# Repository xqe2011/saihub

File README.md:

<h1 align="center">
   SAIHub
</h1>

<p align="center"><strong>Give your agent a hand.</strong></p>

<p align="center">
  An MIT-licensed, agent-ready IO board.<br>
  ESP32-C5 firmware that speaks <a href="https://modelcontextprotocol.io/">MCP</a>,
  so Cursor, Claude Code, and Codex can drive real hardware.
</p>

<p align="center">
  <a href="README.zh.md">中文</a>
  · <a href="docs/cookbook.md">Cookbook</a>
  · <a href="docs/hardware.md">Hardware</a>
  · <a href="docs/design-notes.md">Protocol</a>
  · <a href="docs/build.md">Build</a>
  · <a href="https://github.com/xqe2011/saihub/releases">Releases</a>
  · <a href="LICENSE">MIT</a>
</p>

<p align="center">
  Watch the video: <a href="https://youtu.be/VpJexyDZVVk"> YouTube</a>
  · <a href="https://www.bilibili.com/video/BV1MVn66EEgq"> Bilibili</a>
</p>

---

## What it is

SAIHub is a pocket IO and debug companion for coding agents. Flash it, join Wi-Fi, paste an MCP URL, and the agent gets a hand on real hardware:

- **Wireless flashing & debugging** — expose CMSIS-DAP (SWD) and RFC2217 (serial-over-TCP) on the LAN or through the cloud relay, so OpenOCD, GDB, and serial flashers can program and step-debug targets like STM32, RP2040, nRF52, Arduino, or ESP32 remotely.
- **Bus debugging & emulation** — probe and drive UART, SPI, and I2C buses directly, or run SPI and I2C in slave mode to capture bus transactions from the target and emulate sensors or peripherals with programmable response maps.
- **GPIO / PWM / trace / programmable power** — toggle pins, generate pulses and PWM up to 50 kHz, capture multi-pin edges like a logic analyzer, and switch fault-protected 3.3 V / 5 V rails on and off, all over MCP.
- **On-device scripting** — the agent can upload Lua scripts and run them on the board itself, so timing-critical or multi-step logic executes locally without a network round-trip per operation.

The board is **SAIHub-Mini**: 48 × 28 mm, ESP32-C5, USB-C, a 12-pin header, fault-latched programmable 3.3 V / 5 V outputs, and an onboard buzzer. Pinout and electrical details: [docs/hardware.md](docs/hardware.md). Firmware, KiCad design, and the relay server all live in this repo.

You do not have to use our board — the firmware runs on any ESP32-C5. See [bring your own board](docs/bring-your-own-board.md) for what changes and where to remap the GPIOs.

## What you can do with it

**Zero-PC firmware development with cloud agents.** You don't even need a computer at the bench. Power SAIHub from a USB charger, wire it to your target board, and connect **Cursor Cloud Agents**, **Claude Code cloud sessions**, or **OpenAI Codex Cloud** through the cloud relay. Running entirely in the cloud, the agent can:

1. **Provision the build & debug environment** in its cloud sandbox — install toolchains, OpenOCD, GDB, or serial flashers, then write and compile the firmware.
2. **Remotely flash and step-debug** the target over tunneled CMSIS-DAP (SWD) or RFC2217 serial-over-TCP.
3. **Automated hardware testing** — power-cycle the 3.3 V / 5 V rails, watch pin signals and PWM timing with `trace_pins`, inspect UART logs, capture SPI/I2C traffic, or **fake SPI/I2C sensors** in slave mode to verify driver behavior against synthetic data.
4. **Deliver tested, runnable firmware** directly in a pull request — verified on real hardware with zero manual probing or local setup.

**Give your local agent a hand on the bench.** Drop SAIHub next to a target board and let Cursor, Claude Code, or Codex CLI drive GPIO, generate PWM, capture waveforms, probe I2C/SPI, and flash over SWD/UART instead of asking you to move jumpers and scope probes by hand.

**An agent-ready IO board.** The simplest way to hang real-world IO off an agent:

- Sweep a **servo** from a Lua script while the agent watches the mechanism.
- Dim a **light**, blink a status LED over PWM, or chime the onboard **buzzer** when a build or test finishes.
- Close an **electromagnetic relay** to switch a pump, a lock, or a heater.
- Power a 3.3 V or 5 V sensor from the switched, fault-protected rails, then read it over I2C, SPI, UART, or GPIO.

## Quick start

The [cookbook](docs/cookbook.md) walks through every step:

1. Open the [SAIHub web flasher](https://xqe2011.github.io/saihub) in Chrome or Edge, pick a release, and flash the board.
2. Click **BOOT** to open Wi-Fi pairing, join the `SAIHUB-xxxxxx` AP, and pick your network.
3. Point Cursor / Claude Code / Codex CLI at `http://<device-ip>/mcp`. The agent now has a hand on your bench.

## Ways to connect

The LAN URL is all you need at the bench. To reach the board from anywhere, put a relay in front of it — our managed cloud, or one you deploy yourself:

| | Local LAN | Self-hosted relay | Managed cloud |
| --- | --- | --- | --- |
| Best for | Bench work, zero setup | Remote access under your own account | Remote access, zero ops |
| MCP URL | `http://<device-ip>/mcp` | `https://<your-worker>/device/<digest>/mcp` | `https://saihub.xqe2011.com/device/<digest>/mcp` |
| Reach | Same LAN only | Anywhere | Anywhere |
| Setup | None after Wi-Fi | Deploy to Cloudflare then rebuild firmware with your origin ([details](docs/cookbook.md#5-self-host-the-cloudflare-relay)) | None — boards bought from us connect to the managed cloud |
| Auth | None (LAN trust) | OAuth through your relay | OAuth in the browser |
| Traffic path | Direct to the board | Through your Cloudflare account | Through our infrastructure |
| Cost | Free | Cloudflare free tier | Included with the board |

After the board authenticates with the relay, the serial log prints its landing page — `https://<origin>/cloud/landing/<digest>/page` — with live online status, copyable MCP or REST/OpenAPI URLs, and a button to mint a authentication token.

The relay protocol is server-agnostic — the Cloudflare Worker in this repo is the reference implementation ([design notes](docs/design-notes.md)).

## No vendor lock-in

Nothing here ties you to us:

- **Any ESP32-C5 board works.** SAIHub-Mini is just one carrier; an off-the-shelf DevKit or your own PCB runs the same firmware. See [bring your own board](docs/bring-your-own-board.md).
- **You don't need our managed cloud.** The relay is a Cloudflare Worker you can deploy under your own account — or replace entirely, since the protocol is documented and server-agnostic.
- **Everything is open source under MIT.** Firmware, KiCad hardware design, and the cloud relay all live in this repo.
- **LAN mode needs no service at all.** Wi-Fi plus the local MCP URL is a complete setup; the cloud is optional convenience, not a requirement.

## Capabilities

| Area | What the agent gets |
| --- | --- |
| GPIO 0–7 | Digital in / out / open-drain, microsecond pulse, PWM up to 50 kHz |
| Trace | Edge capture on one or more pins (up to 60 s), like a pocket logic analyzer |
| SWD debug | CMSIS-DAP over TCP for OpenOCD / GDB on LAN or cloud relay |
| UART | One product UART with RTS / DTR for auto-flashing circuits, plus RFC2217 serial-over-TCP |
| SPI | Master (up to 10 MHz) and Slave — capture, generate, and emulate bus traffic |
| I2C | Master (up to 1 MHz) and Slave, 7 / 10-bit addressing — capture, generate, and emulate bus traffic |
| Power | Switched **3V3** and **5V** rails with overcurrent / fault protection |
| Buzzer | Onboard Morse-code passive buzzer |

Logic pins are **3.3 V only** — full electrical limits in [docs/hardware.md](docs/hardware.md).

## Repo layout

| Path | What |
| --- | --- |
| `main/` | ESP-IDF firmware (ESP32-C5, IDF ≥ 5.5) |
| `mcp.json` | MCP tool schema served by the device |
| `openapi.json` | REST API for the same tools |
| `cloud/cloudflare/` | Cloudflare Worker relay + OAuth (reference server) |
| `hardware/` | SAIHub-Mini KiCad project |
| `docs/` | Cookbook, hardware, build, protocol, and BYO-board docs |

## Community

- [Join our Discord](https://discord.gg/aZerprjxsc)
- QQ group: **499504696**

## License

[MIT](LICENSE).

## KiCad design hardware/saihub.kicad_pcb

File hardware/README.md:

# SAIHub-Mini — Rev A

Version: **2026-09-24**. Author: **GPT6-Astra**. Co-author: **xqe2011**.

The date version changes only with explicit user permission. See [the version log](docs/version-log.md); regeneration and exports preserve the approved version.

**Current state: front-only layout, locally routed and CAD validated.** All 64 components are on the front surface. Electrical, physical, schematic-parity and connectivity checks report zero findings.

The local routing is complete, including both header ground contacts. R6 moves into the space freed beside U10 to open the capacitor ground connection. R19 and R22 occupy the right-side lane, with U2 shifted 0.6 mm left; R9, R11, R12 and TP3 are repositioned for routing. J1, J2, SW1, U3 and D4-D7 are locked at their approved positions and orientations, preserving the enclosure interfaces.

U10 now shares TPD4E05U06DQAR with U6/U7. Two channels shunt the switched outputs to ground; its former supply-reference bypass C21 is removed. D2 remains on the input. This frees space without changing external interfaces; board-level transient protection still requires qualification.

Editable KiCad 10 design for the SAIHub IO controller. Open `saihub.kicad_pro`; symbols and footprints are project-local. The schematic is one A2 page with seven functional sections. Related parts are wired together within each section; the header and its protection share one section.

The PCB remains **48 × 28 mm**, with 64 footprints: all on the front (top) surface. Across the front edge, left to right: **12-pin header → BOOT button → USB-C**. Connector pins and the switch actuator project beyond the PCB outline.

SW1 follows the supplied **2X4 side-push switch drawing**, including two **0.75 mm non-plated locating holes on 1.7 mm centres**. The stepped mounting lands and two electrical contacts are retained; the actuator faces the connector edge. See [the supplied drawing](agent/docs/button-2x4.pdf). Confirm the procurement variant against this drawing.

The **16 × 24 mm module has a built-in PCB antenna at the bottom-left corner**. Its body spans x=0.85–16.85 mm and y=4–28 mm. An open notch removes the board beneath the antenna at y=20.5–28 mm and x=0–21.85 mm: it opens to the left and bottom edges and leaves **5 mm to the antenna's right**. The 0.85 mm body inset at the left preserves solder-land and copper-edge clearance beside the module's connected section. No board material or copper remains beneath the antenna. Enclosure clearance still needs verification.

The 5 V / 3 A input, nominal 1 A output protection, regulator and buzzer are retained. IO3 and IO7 now use internal pins 2 and 7; the firmware mapping changes with this board. Earlier hardware must use its matching firmware mapping.

## Files

- `saihub.kicad_pro`, `saihub.kicad_sch`, `saihub.kicad_pcb`: open the project in KiCad 10 to edit the current design.
- `libraries/`, `sym-lib-table`, `fp-lib-table`: project-local symbols and footprints required by KiCad.
- `docs/bom.csv`: current procurement BOM; excludes test pads; no external antenna accessory is required.
- `docs/bom.html`: self-contained interactive assembly BOM from [InteractiveHtmlBom](https://github.com/openscopeproject/InteractiveHtmlBom), with component lookup, MPNs, copper and net highlighting. Test pads are visible on the board but excluded from the BOM table.
- `docs/schematic.pdf`: schematic review.
- `docs/pcb.pdf`: top and mirrored bottom PCB previews, including package-body drawings on fabrication and silkscreen layers, plus designators.
- `docs/shell.pdf`: enclosure previews with/without the board, dimensioned views and ABS mass estimate; refresh after every PCB change.
- `mechanical/`: editable build123d enclosure, board reference, STEP/STL exports and drawing generators; see [the mechanical guide](mechanical/README.md).
- `docs/version-log.md`: approved version and permission policy.
- `agent/`: regeneration scripts, design metadata, design notes, validation evidence, routing intermediates and reusable workflow skills.

Current validation and routing inputs are retained in Git. `agent/previews/` contains regenerable images and is ignored; the review PDFs are committed. KiCad local history, locks, backups and personal settings are also ignored.

**Prototype status:** CAD routing checks pass; the board has not been fabricated or bench tested. Verify thermal behavior, supply loading and USB operation using `agent/docs/prototype-test.md`. The 26.1 kΩ ILIM resistors set approximately 0.989 A nominal, with 0.908–1.081 A bounds including resistor tolerance; a guaranteed 1 A continuous rating is not implied.

## Connections

J2 pin 1 is square and marked `3V3`. Looking at the top with the connector edge at the top, pins run left to right:

`1:3V3_SW  2:GND  3:5V_SW  4:GND  5:IO0  6:IO1  7:IO2  8:IO3  9:IO4  10:IO5  11:IO6  12:IO7`

IO0-IO7 map to GPIO **10, 1, 0, 2, 4, 5, 6, 7**. Logic pins are **3.3 V only**; the 1 A setting applies to the two power channels. GPIO8 enables 3.3 V output and GPIO9 enables 5 V output. Both default off. Do not back-power either rail. The 5 V output follows USB voltage minus fuse, trace and switch losses.

Four **0603 (1.6 × 0.8 mm)** LEDs form one top-side column, with matching shell openings and recessed labels:
**3V3 OUT** and **5V OUT** are green and monitor the switched outputs; **5V IN** is red
and monitors input power after the fuse; **STATUS** is blue and connects to control
pin 26 (active high). The blue indicator requires firmware control; no behavior is
assigned by this hardware change. R19-R22 share one 660 ohm, 1%, 0603 resistor type (one resistor per LED). Brightness differs by color and supply voltage; verify it on the prototype. R7-R10 and R19-R22 are assembled on the front, like every other component.

GPIO12 drives the passive 5020 buzzer at 4 kHz / 50% duty. GPIO13/14 carry USB D-/D+. BOOT is GPIO28. TP1/TP2 are EN/GND reset pads on the top: briefly short them to reset. Hold BOOT during reset/power-on for download recovery. TP3 is UART TX on the front, TP4 always-on 3.3 V, and TP5/TP6 active-low switch fault outputs.

Use a specified **5 V / 3 A adapter and cable** for external loads. Keep outputs off on unqualified PC ports. No PD, OTG or source-current detection is implemented. The antenna is built into the module. See `agent/docs/design-notes.md` for SGM6232 input-voltage margin and sourcing status.

## Rebuilding

Normal edits can be made in KiCad. From the repository root, run:

```sh
export INTERACTIVE_HTML_BOM=/path/to/InteractiveHtmlBom/InteractiveHtmlBom/generate_interactive_bom.py
python3 hardware/agent/scripts/export_placement.py --routed
```

The command projects package-body drawings from Fab onto both silkscreen layers, clips them around pads, and places designators, synchronizes board metadata, requires zero ERC/DRC/parity findings and zero unconnected items, then refreshes the five files in `docs/`, including `shell.pdf`. It requires KiCad 10, ImageMagick and Python `reportlab` (`python3 -m pip install reportlab`). Set `KICAD_CLI` and `KICAD_PYTHON` to override the macOS tool defaults; the latter must provide `pcbnew`. Poppler is optional for the separate schematic PNG. Clone [InteractiveHtmlBom](https://github.com/openscopeproject/InteractiveHtmlBom) and set `INTERACTIVE_HTML_BOM` as above (validated at commit `5c192e794cd66fde04bab11810601b711bf8581b`). On macOS, its generator requires a logged-in desktop session. `agent/scripts/export_ibom.py` can refresh only `docs/bom.html`.

`agent/scripts/export_docs.py` refreshes the review documents and the enclosure reference/exports, without modifying the board or schematic. It runs the enclosure geometry checks but does not replace electrical CAD validation. Install `mechanical/requirements.txt` into `mechanical/.venv`, or set `MECHANICAL_PYTHON` to that environment. Every PCB update requires reconciling the enclosure parameters and regenerating `docs/shell.pdf`; the document exporter calls `mechanical/refresh_shell.py` automatically and fails if that refresh fails. `agent/scripts/export.py` separately validates and exports fabrication files into `manufacturing/`.

For regeneration and routing, read [the project workflow skill](agent/skills/kicad-workflow/SKILL.md). `generate.py` writes the separate `agent/routing/saihub-unrouted.kicad_pcb`; it preserves the main routed PCB but regenerates the schematic and libraries while preserving existing project settings. The saved copper snapshot matches this front-only placement and preserves the actual ground-pour settings and pad connections. The legacy SES file predates this placement and must not be imported.

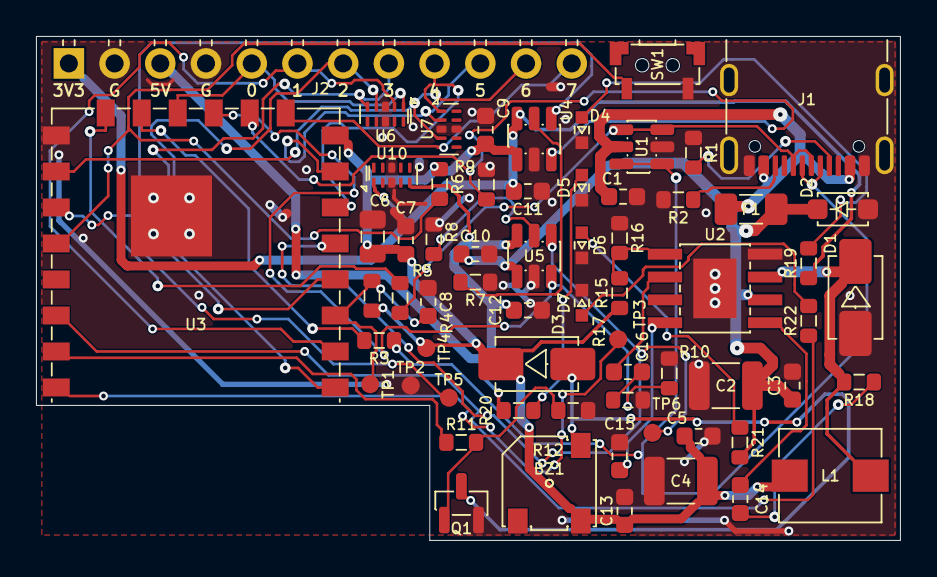
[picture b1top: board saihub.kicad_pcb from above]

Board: 2 copper layers, 48.0 x 28.0 mm, 64 parts (0 on the bottom side), 44 nets.

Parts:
BZ1: 5020 3V 4kHz; Buzzer_5020_Supplied
C1, C3, C5, C7, C9, C10, C13, C15: 100n; C_0603_1608Metric
C2: 22u; C_1210_3225Metric
C4: 47u; C_1210_3225Metric
C6: 10u; C_0805_2012Metric
C8, C11, C12: 1u; C_0603_1608Metric
C14: 10n; C_0603_1608Metric
C16: 5.6n; C_0603_1608Metric
D1, D3: SS34; D_SMA
D2: SMF5.0A; D_SOD-123F
D4, D5: GREEN; LED_0603_1608Metric
D6: RED; LED_0603_1608Metric
D7: BLUE; LED_0603_1608Metric
F1: 3A fuse; Fuse_1206_3216Metric
J1: USB4105-GF-A; USB_C_Receptacle_GCT_USB4105-xx-A_16P_TopMnt_Horizontal
J2: 1x12 2.54mm right-angle; PinHeader_1x12_P2.54mm_Horizontal
L1: 4.7uH; SRP5030TA
Q1: AO3400A; SOT-23
R1, R2: 5.1k; R_0603_1608Metric
R3, R4: 22; R_0603_1608Metric
R5, R6, R9, R10, R12, R17: 10k; R_0603_1608Metric
R7, R8: 26.1k; R_0603_1608Metric
R11: 100; R_0603_1608Metric
R15: 33k; R_0603_1608Metric
R16: 10.5k; R_0603_1608Metric
R18: 10; R_0603_1608Metric
R19, R20, R21, R22: 660; R_0603_1608Metric
SW1: BOOT; SW_SPST_2X4_LocatingPins
TP1: EN; TestPoint_Pad_D1.0mm
TP2: GND; TestPoint_Pad_D1.0mm
TP3: UART_TX; TestPoint_Pad_D1.0mm
TP4: V3V3; TestPoint_Pad_D1.0mm
TP5: FAULT4; TestPoint_Pad_D1.0mm
TP6: FAULT5; TestPoint_Pad_D1.0mm
U1: USBLC6-2SC6; SOT-23-6
U2: SGM6232YPS8G/TR; SGM6232_SOIC8_EP
U3: ESPC5-12-H4
U4, U5: TPS2553DDBVR; SOT-23-6
U6, U7, U10: TPD4E05U06DQAR; TPD4E05U06_DQA

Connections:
BOOT: R6.2, SW1.1, U3.18
BOOT_R: C14.1, R18.2
BS: C14.2, U2.1
BUZZ_GATE: Q1.1, R11.2, R12.1
BUZZ_LOW: BZ1.2, D3.2, Q1.3
BUZZ_PWM: R11.1, U3.21
CC1: J1.A5, R1.1
CC2: J1.B5, R2.1
COMP: C16.1, U2.6
COMP_RC: C16.2, R17.1
D4_A: D4.1, R19.2
D5_A: D5.1, R20.2
D6_A: D6.1, R21.2
D7_A: D7.1, R22.2
EN: C8.1, R5.2, TP1.1, U3.3
FAULT4: TP5.1, U3.17, U4.4
FAULT5: TP6.1, U3.5, U5.4
FB: R15.2, R16.1, U2.5
GND: C1.2, C2.2, C3.2, C4.2, C5.2, C6.2, C7.2, C8.2, C9.2, C10.2, C11.2, C12.2, C13.2, C15.2, D1.2, D2.2, D4.2, D5.2, D6.2, D7.2, J1.A1, J1.A12, J1.B1, J1.B12, J1.SH, J2.2, J2.4, Q1.2, R1.2, R2.2, R7.2, R8.2, R9.2, R10.2, R12.2, R16.2, R17.2, SW1.2, TP2.1, U1.2, U2.4, U2.9, U3.15, U3.23, U4.2, U5.2, U6.3, U6.8, U7.3, U7.8, U10.3, U10.8
ILIM4: R7.1, U4.5
ILIM5: R8.1, U5.5
IO0: J2.5, U3.12, U6.1
IO1: J2.6, U3.2, U6.2
IO2: J2.7, U3.1, U6.4
IO3: J2.8, U3.4, U6.5
IO4: J2.9, U3.6, U7.1
IO5: J2.10, U3.7, U7.2
IO6: J2.11, U3.16, U7.4
IO7: J2.12, U3.9, U7.5
MCU_DM: R3.2, U3.13
MCU_DP: R4.2, U3.14
PWR3_EN: R9.1, U3.10, U4.3
PWR5_EN: R10.1, U3.11, U5.3
SS: C15.1, U2.8
STATUS_LED: R22.1, U3.20
SW: D1.1, L1.1, R18.1, U2.3
UART_TX: TP3.1, U3.22
USB_DM: J1.A7, J1.B7, R3.1, U1.1, U1.6
USB_DP: J1.A6, J1.B6, R4.1, U1.3, U1.4
V3V3: BZ1.1, C4.1, C5.1, C6.1, C7.1, C9.1, C13.1, D3.1, L1.2, R5.1, R6.1, R15.1, TP4.1, U3.8, U4.1
V3_SW: C11.1, J2.1, R19.1, U4.6, U10.1
V5: C2.1, C3.1, C10.1, D2.1, F1.2, R21.1, U2.2, U5.1
V5_SW: C12.1, J2.3, R20.1, U5.6, U10.5
VBUS: C1.1, F1.1, J1.A4, J1.A9, J1.B4, J1.B9, U1.5

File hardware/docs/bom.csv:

Reference,Quantity,Value,MPN_or_procurement_spec,Footprint,Notes,Datasheet
J1,1,USB4105-GF-A,USB4105-GF-A,Saihub:USB_C_Receptacle_GCT_USB4105-xx-A_16P_TopMnt_Horizontal,; top assembly,https://gct.co/files/drawings/usb4105.pdf
"R1, R2",2,5.1k,"Generic 5.1k ohm, 1%, 0603, >=0.1W",Saihub:R_0603_1608Metric,"1%, 0603; top assembly",
"U1, U10",2,USBLC6-2SC6,USBLC6-2SC6,Saihub:SOT-23-6,; top assembly; Header power ESD shunt; place beside J2 with short ground return; top assembly,https://www.st.com/resource/en/datasheet/usblc6-2.pdf
"C1, C3, C5, C7, C9, C10, C13, C15, C21",9,100n,"Generic 100nF, X7R, >=10V, +/-10%, 0603",Saihub:C_0603_1608Metric,"X7R, 10V minimum; top assembly; X7R, 10V minimum; local ESD supply bypass; top assembly",
"R3, R4",2,22,"Generic 22 ohm, 1%, 0603, >=0.1W",Saihub:R_0603_1608Metric,"1%, 0603; top assembly",
F1,1,3A fuse,0467003.NR,Saihub:Fuse_1206_3216Metric,"Littelfuse 467, 3A fast fuse; top assembly",https://www.littelfuse.com/~/media/electronics/datasheets/fu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
D2,1,SMF5.0A,SMF5.0A,Saihub:D_SOD-123F,; top assembly,https://www.yint-electronic.com/products/emsproduct/tvs/smf5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
U2,1,SGM6232YPS8G/TR,SGM6232YPS8G/TR,Saihub:SGM6232_SOIC8_EP,EN open for auto-start; 3.314V divider; exposed pad GND; top assembly,https://www.sg-micro.com/rect/assets/9fe04e94-334c-4982-964b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
L1,1,4.7uH,SRP5030TA-4R7M,Saihub:SRP5030TA,"Shielded 5.7x5.2x2.8mm; 4.6A Irms, 6A Isat per manufacturer drawing; top assembly",https://bourns.com/docs/product-datasheets/SRP5030TA.pdf
"D1, D3",2,SS34,SS34,Saihub:D_SMA,"MDD SS34, 40V / 3A, SMA (DO-214AC); do not substitute SMC variants; top assembly",https://datasheet.lcsc.com/datasheet/pdf/dfa1ff67dea875d0135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
C2,1,22u,"Generic 22uF, X7R, >=10V, +/-10%, 1210",Saihub:C_1210_3225Metric,"X7R, 10V minimum; top assembly",
C4,1,47u,"Generic 47uF, X7R, >=10V, +/-10%, 1210",Saihub:C_1210_3225Metric,"X7R, 10V minimum; top assembly",
R15,1,33k,"Generic 33k ohm, 1%, 0603, >=0.1W",Saihub:R_0603_1608Metric,"1%, 0603; top assembly",
R16,1,10.5k,"Generic 10.5k ohm, 1%, 0603, >=0.1W",Saihub:R_0603_1608Metric,"1%, 0603; top assembly",
"R5, R6, R9, R10, R12, R17",6,10k,"Generic 10k ohm, 1%, 0603, >=0.1W",Saihub:R_0603_1608Metric,"1%, 0603; top assembly; 1%, 0603; bottom assembly",
R18,1,10,"Generic 10 ohm, 1%, 0603, >=0.1W",Saihub:R_0603_1608Metric,"1%, 0603; top assembly",
C14,1,10n,"Generic 10nF, X7R, >=10V, +/-10%, 0603",Saihub:C_0603_1608Metric,"X7R, 10V minimum; top assembly",
C16,1,5.6n,"Generic 5.6nF, X7R, >=10V, +/-10%, 0603",Saihub:C_0603_1608Metric,"X7R, 10V minimum; top assembly",
U3,1,ESPC5-12-H4,ESPC5-12-H4,Saihub:ESPC5-12-H4,16 x 24 mm module; built-in PCB antenna over bottom-left board cutout; top assembly,https://atta.szlcsc.com/upload/public/pdf/source/20251016/3D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
C6,1,10u,"Generic 10uF, X7R, >=10V, +/-10%, 0805",Saihub:C_0805_2012Metric,"X7R, 10V minimum; top assembly",
"C8, C11, C12",3,1u,"Generic 1uF, X7R, >=10V, +/-10%, 0603",Saihub:C_0603_1608Metric,"X7R, 10V minimum; top assembly",
SW1,1,BOOT,2X4,Saihub:SW_SPST_2X4_LocatingPins,Side-push; two 0.75 mm locating holes on 1.7 mm centres; supplied 2X4 drawing; top assembly,${KIPRJMOD}/agent/docs/button-2x4.pdf
J2,1,1x12 2.54mm right-angle,61301211021,Saihub:PinHeader_1x12_P2.54mm_Horizontal,Wurth WR-PHD 2.54mm 1x12 right-angle male; top assembly,https://www.we-online.com/components/products/datasheet/6130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
"U4, U5",2,TPS2553DDBVR,TPS2553DDBVR,Saihub:SOT-23-6,; top assembly,https://www.ti.com/lit/ds/symlink/tps2553d.pdf
"R7, R8",2,26.1k,"Generic 26.1k ohm, 1%, 0603, >=0.1W",Saihub:R_0603_1608Metric,"1%, 0603; bottom assembly",
BZ1,1,5020 3V 4kHz,5020 supplied specification (MPN unspecified),Saihub:Buzzer_5020_Supplied,"5.2 x 5.2 x 2 mm; 3 V nominal, 2-4 V operating, 4 kHz, 100 mA max; derived lands require assembler review; top assembly",${KIPRJMOD}/agent/docs/buzzer-5020-supplied.png
Q1,1,AO3400A,AO3400A,Saihub:SOT-23,; top assembly,https://www.aosmd.com/sites/default/files/res/datasheets/AO3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
R11,1,100,"Generic 100 ohm, 1%, 0603, >=0.1W",Saihub:R_0603_1608Metric,"1%, 0603; top assembly",
"D4, D5",2,GREEN,KT-0603G,Saihub:LED_0603_1608Metric,"0603 indicator; 1.6 x 0.8 x 0.6 mm; anode pad 1, cathode pad 2; top assembly",${KIPRJMOD}/agent/docs/led-kt-0603g.pdf
"R19, R22",2,330,"Generic 330 ohm, 1%, 0603, >=0.1W",Saihub:R_0603_1608Metric,"1%, 0603; bottom assembly",
R20,1,1.2k,"Generic 1.2k ohm, 1%, 0603, >=0.1W",Saihub:R_0603_1608Metric,"1%, 0603; bottom assembly",
D6,1,RED,KT-0603R,Saihub:LED_0603_1608Metric,"0603 indicator; 1.6 x 0.8 x 0.6 mm; anode pad 1, cathode pad 2; top assembly",${KIPRJMOD}/agent/docs/led-kt-0603r.pdf
R21,1,1.5k,"Generic 1.5k ohm, 1%, 0603, >=0.1W",Saihub:R_0603_1608Metric,"1%, 0603; bottom assembly",
D7,1,BLUE,KT-0603B,Saihub:LED_0603_1608Metric,"0603 indicator; 1.6 x 0.8 x 0.6 mm; anode pad 1, cathode pad 2; top assembly",${KIPRJMOD}/agent/docs/led-kt-0603b.pdf
"U6, U7",2,TPD4E05U06DQAR,TPD4E05U06DQAR,Saihub:TPD4E05U06_DQA,Four GPIO ESD shunts; USON-10 2.5x1mm; no supply required; top assembly,https://www.ti.com/lit/ds/symlink/tpd4e05u06.pdf
